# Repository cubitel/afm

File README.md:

DIY Atomic Force Microscope
---------------------------

DIY Atomic Force Microscope / Scanning Tunneling Microscope project.
More information can be found in [Project page](http://npk.cubitel.org/?/hardware/afm) (in Russian).

Please note that this project is under development yet.

### Hardware

Hardware folder contains hardware design files.

_Design tools_
- Schematic, PCB -- KiCAD
- 3D parts -- FreeCAD

### Firmware

Firmware folder contains firmware source files for STM32F407 controller.
Firmware using FreeRTOS and STM32 USB stack (bundled with the source tree).

### Software

Software folder contains control application source files.
Software using wxWidgets and libusb and designed to be cross-platform,
but current Makefile assumes Windows/MinGW.

_Build requirements_
- TDM-GCC
- wxWidgets
- libusb

### License
GPLv3

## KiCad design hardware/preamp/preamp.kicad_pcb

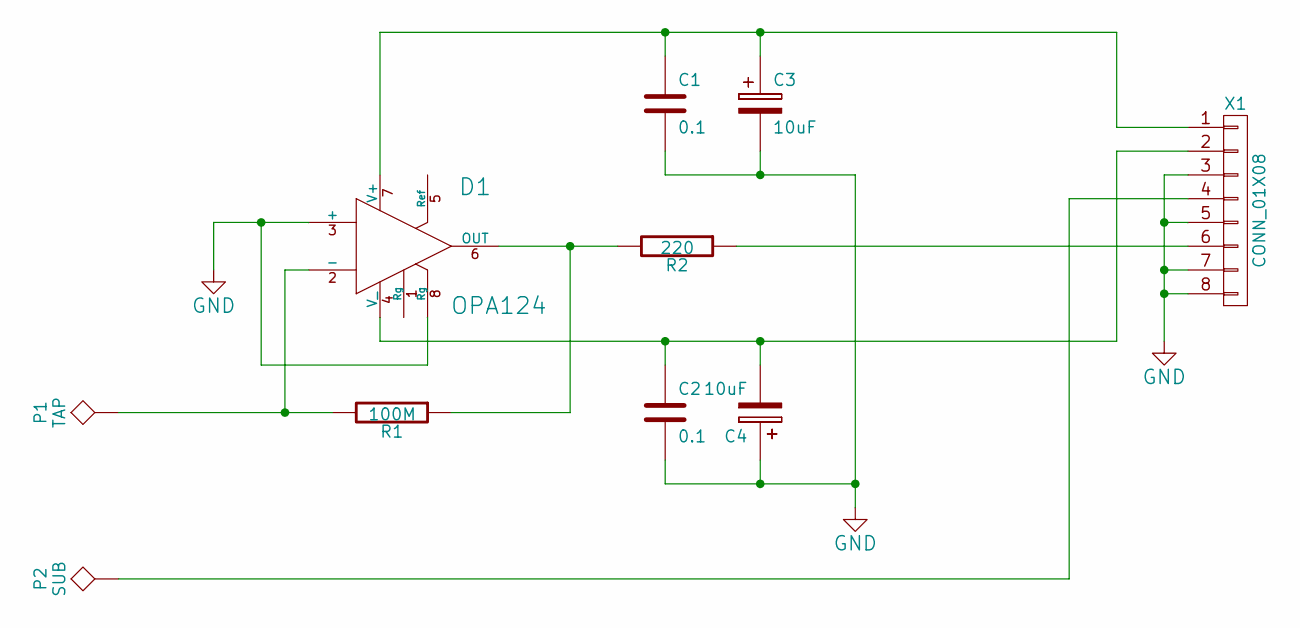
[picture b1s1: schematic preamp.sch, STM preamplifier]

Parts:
C1, C2: 0.1; C_0805
C3, C4: 10uF; TantalC_SizeA_EIA-3216_HandSoldering
D1: OPA124; SOIC-8-N
P1: TAP; Pin_Header_Straight_1x01
P2: SUB; Pin_Header_Straight_1x01
R1: 100M; R_0805
R2: 220; R_0805
X1: CONN_01X08; Pin_Header_Straight_1x08

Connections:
GND: C1.2, C2.2, C3.2, C4.1, D1.3 (+), D1.8 (Rg), X1.3, X1.5, X1.7, X1.8
unnamed: C1.1, C3.1, D1.7 (V+), X1.1
unnamed: C2.1, C4.2, D1.4 (V_), X1.2
unnamed: D1.2 (-), P1.1, R1.2
unnamed: D1.6 (OUT), R1.1, R2.2
unnamed: P2.1, X1.4
unnamed: R2.1, X1.6

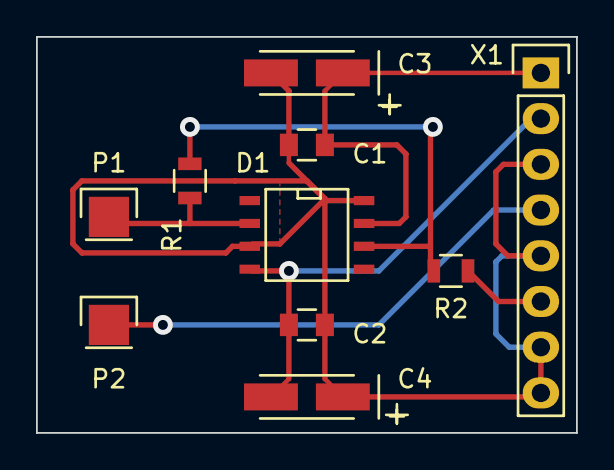
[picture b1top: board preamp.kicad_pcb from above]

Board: 2 copper layers, 30.0 x 22.0 mm, 10 parts (0 on the bottom side), 7 nets.

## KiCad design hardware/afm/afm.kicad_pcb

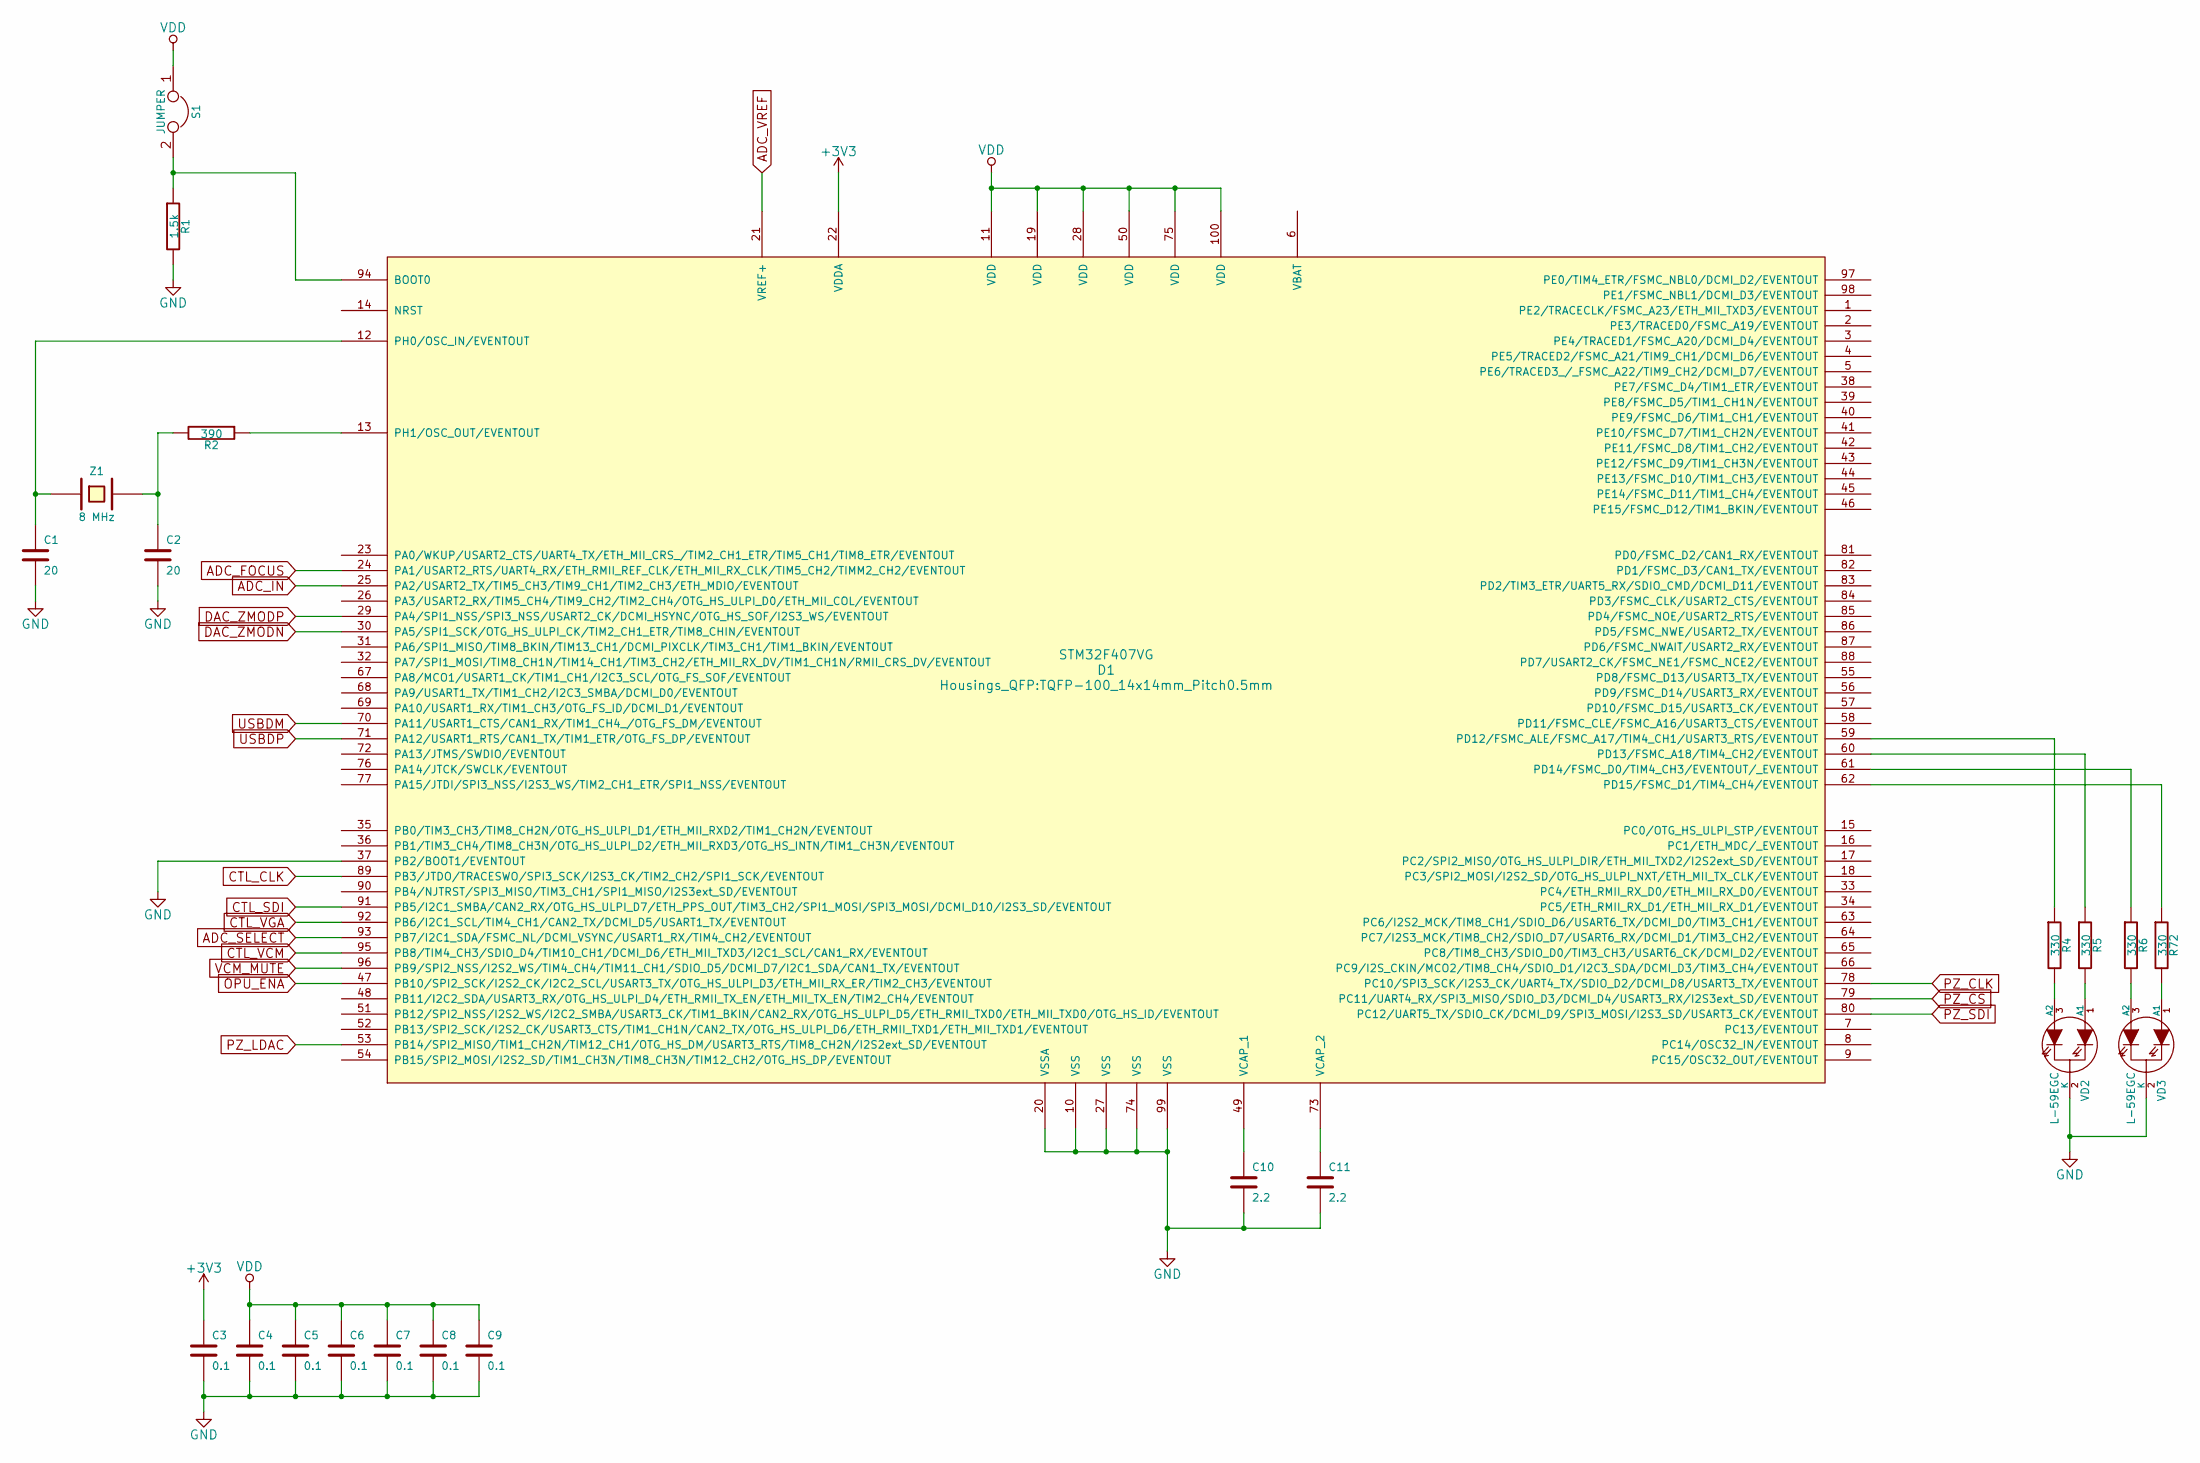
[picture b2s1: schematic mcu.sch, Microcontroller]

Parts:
C1, C2: 20; C_0603_HandSoldering
C3, C4, C5, C6, C7, C8, C9: 0.1; C_0603_HandSoldering
C10, C11: 2.2; C_0805_HandSoldering
D1: STM32F407VG; TQFP-100_14x14mm_Pitch0.5mm
R1: 1.5k; R_0603_HandSoldering
R2: 390; R_0603_HandSoldering
R4, R5, R6, R72: 330; R_0603_HandSoldering
S1: JUMPER; Pin_Header_Straight_1x02
VD2, VD3: L-59EGC; LED-5MM-3
Z1: 8 MHz; Crystal_HC49-SD_SMD

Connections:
+3V3: C3.1, D1.22 (VDDA); also elsewhere on the board
ADC_FOCUS: D1.24 (PA1/USART2_RTS/UART4_RX/ETH_RMII_REF_CL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); also elsewhere on the board
ADC_IN: D1.25 (PA2/USART2_TX/TIM5_CH3/TIM9_CH1/TIM2_CH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); also elsewhere on the board
ADC_SELECT: D1.93 (PB7/I2C1_SDA/FSMC_NL/DCMI_VSYNC/USART1_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); also elsewhere on the board
ADC_VREF: D1.21 (VREF+); also elsewhere on the board
CTL_CLK: D1.89 (PB3/JTDO/TRACESWO/SPI3_SCK/I2S3_CK/TIM2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); also elsewhere on the board
CTL_SDI: D1.91 (PB5/I2C1_SMBA/CAN2_RX/OTG_HS_ULPI_D7/ET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); also elsewhere on the board
CTL_VCM: D1.95 (PB8/TIM4_CH3/SDIO_D4/TIM10_CH1/DCMI_D6/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); also elsewhere on the board
CTL_VGA: D1.92 (PB6/I2C1_SCL/TIM4_CH1/CAN2_TX/DCMI_D5/U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); also elsewhere on the board
DAC_ZMODN: D1.30 (PA5/SPI1_SCK/OTG_HS_ULPI_CK/TIM2_CH1_ET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); also elsewhere on the board
DAC_ZMODP: D1.29 (PA4/SPI1_NSS/SPI3_NSS/USART2_CK/DCMI_HS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); also elsewhere on the board
GND: C1.2, C2.2, C3.2, C4.2, C5.2, C6.2, C7.2, C8.2, C9.2, C10.2, C11.2, D1.10 (VSS), D1.20 (VSSA), D1.27 (VSS), D1.37 (PB2/BOOT1/EVENTOUT), D1.74 (VSS), D1.99 (VSS), R1.2, VD2.2 (K), VD3.2 (K); also elsewhere on the board
unnamed: C1.1, D1.12 (PH0/OSC_IN/EVENTOUT), Z1.1
unnamed: C2.1, R2.2, Z1.2
unnamed: C10.1, D1.49 (VCAP_1)
unnamed: C11.1, D1.73 (VCAP_2)
unnamed: D1.13 (PH1/OSC_OUT/EVENTOUT), R2.1
unnamed: D1.59 (PD12/FSMC_ALE/FSMC_A17/TIM4_CH1/USART3_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), R4.1
unnamed: D1.60 (PD13/FSMC_A18/TIM4_CH2/EVENTOUT), R5.1
unnamed: D1.61 (PD14/FSMC_D0/TIM4_CH3/EVENTOUT/_EVENTOUT), R6.1
unnamed: D1.62 (PD15/FSMC_D1/TIM4_CH4/EVENTOUT), R72.1
unnamed: D1.94 (BOOT0), R1.1, S1.2
unnamed: R4.2, VD2.3 (A2)
unnamed: R5.2, VD2.1 (A1)
unnamed: R6.2, VD3.3 (A2)
unnamed: R72.2, VD3.1 (A1)
OPU_ENA: D1.47 (PB10/SPI2_SCK/I2S2_CK/I2C2_SCL/USART3_T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); also elsewhere on the board
PZ_CLK: D1.78 (PC10/SPI3_SCK/I2S3_CK/UART4_TX/SDIO_D2/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); also elsewhere on the board
PZ_CS: D1.79 (PC11/UART4_RX/SPI3_MISO/SDIO_D3/DCMI_D4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); also elsewhere on the board
PZ_LDAC: D1.53 (PB14/SPI2_MISO/TIM1_CH2N/TIM12_CH1/OTG_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); also elsewhere on the board
PZ_SDI: D1.80 (PC12/UART5_TX/SDIO_CK/DCMI_D9/SPI3_MOSI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); also elsewhere on the board
USBDM: D1.70 (PA11/USART1_CTS/CAN1_RX/TIM1_CH4_/OTG_F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); also elsewhere on the board
USBDP: D1.71 (PA12/USART1_RTS/CAN1_TX/TIM1_ETR/OTG_FS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); also elsewhere on the board
VCM_MUTE: D1.96 (PB9/SPI2_NSS/I2S2_WS/TIM4_CH4/TIM11_CH1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); also elsewhere on the board
VDD: C4.1, C5.1, C6.1, C7.1, C8.1, C9.1, D1.11 (VDD), D1.19 (VDD), D1.28 (VDD), D1.50 (VDD), D1.75 (VDD), D1.100 (VDD), S1.1; also elsewhere on the board

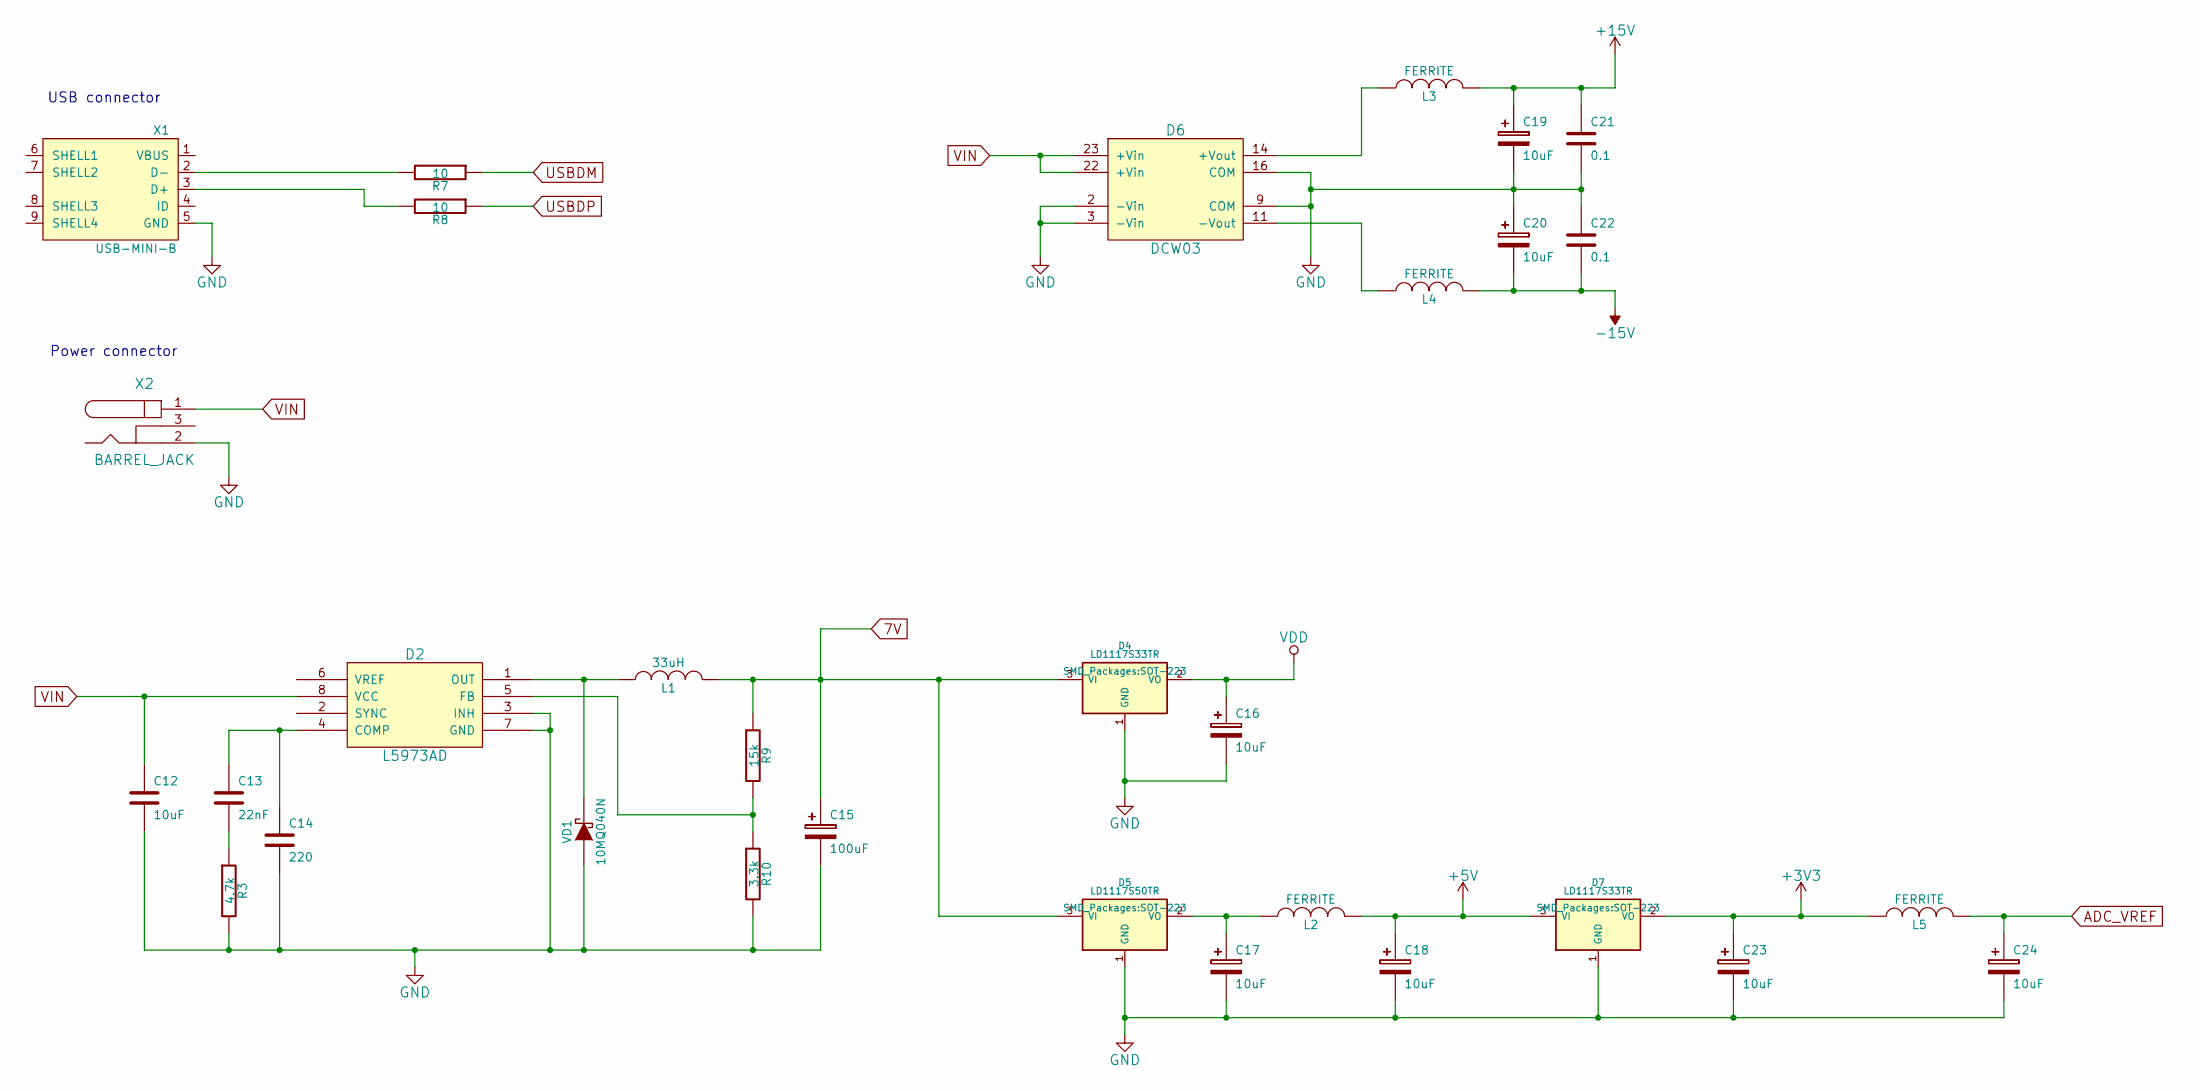
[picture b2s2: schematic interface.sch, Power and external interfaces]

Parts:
C12: 10uF; C_1206_HandSoldering
C13: 22nF; C_0603_HandSoldering
C14: 220; C_0603_HandSoldering
C15: 100uF; TantalC_SizeD_EIA-7343_HandSoldering
C16, C17, C18, C23, C24: 10uF; TantalC_SizeB_EIA-3528_HandSoldering
C19, C20: 10uF; TantalC_SizeD_EIA-7343_HandSoldering
C21, C22: 0.1; C_0603_HandSoldering
D2: L5973AD; SOIC-8-1EP_3.9x4.9mm_Pitch1.27mm
D4, D7: LD1117S33TR; SOT-223
D5: LD1117S50TR; SOT-223
D6: DCW03; DIP-24__600
L1: 33uH; Neosid_Inductor_SM-PIC0612H
L2, L3, L4, L5: FERRITE; R_1206_HandSoldering
R3: 4.7k; R_0603_HandSoldering
R7, R8: 10; R_0603_HandSoldering
R9: 15k; R_0603_HandSoldering
R10: 3.3k; R_0603_HandSoldering
VD1: 10MQ040N; Diode-SMA_Handsoldering
X1: USB-MINI-B; USB_Mini-B
X2: BARREL_JACK; JACK_ALIM

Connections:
7V: C15.1, D4.3 (VI), D5.3 (VI), L1.2, R9.1
+3V3: C23.1, D7.2 (VO), L5.1; also elsewhere on the board
+5V: C18.1, D7.3 (VI), L2.2; also elsewhere on the board
+15V: C19.1, C21.1, L3.2; also elsewhere on the board
-15V: C20.2, C22.2, L4.2; also elsewhere on the board
ADC_VREF: C24.1, L5.2; also elsewhere on the board
GND: C12.2, C14.2, C15.2, C16.2, C17.2, C18.2, C19.2, C20.1, C21.2, C22.1, C23.2, C24.2, D2.3 (INH), D2.7 (GND), D4.1 (GND), D5.1 (GND), D6.2 (-Vin), D6.3 (-Vin), D6.9 (COM), D6.16 (COM), D7.1 (GND), R3.2, R10.2, VD1.1 (A), X1.5 (GND), X2.2; also elsewhere on the board
unnamed: C13.1, C14.1, D2.4 (COMP)
unnamed: C13.2, R3.1
unnamed: C17.1, D5.2 (VO), L2.1
unnamed: D2.1 (OUT), L1.1, VD1.2 (K)
unnamed: D2.5 (FB), R9.2, R10.1
unnamed: D6.11 (-Vout), L4.1
unnamed: D6.14 (+Vout), L3.1
unnamed: R7.2, X1.2 (D-)
unnamed: R8.2, X1.3 (D+)
USBDM: R7.1; also elsewhere on the board
USBDP: R8.1; also elsewhere on the board
VDD: C16.1, D4.2 (VO); also elsewhere on the board
VIN: C12.1, D2.8 (VCC), D6.22 (+Vin), D6.23 (+Vin), X2.1

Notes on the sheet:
USB connector
Power connector

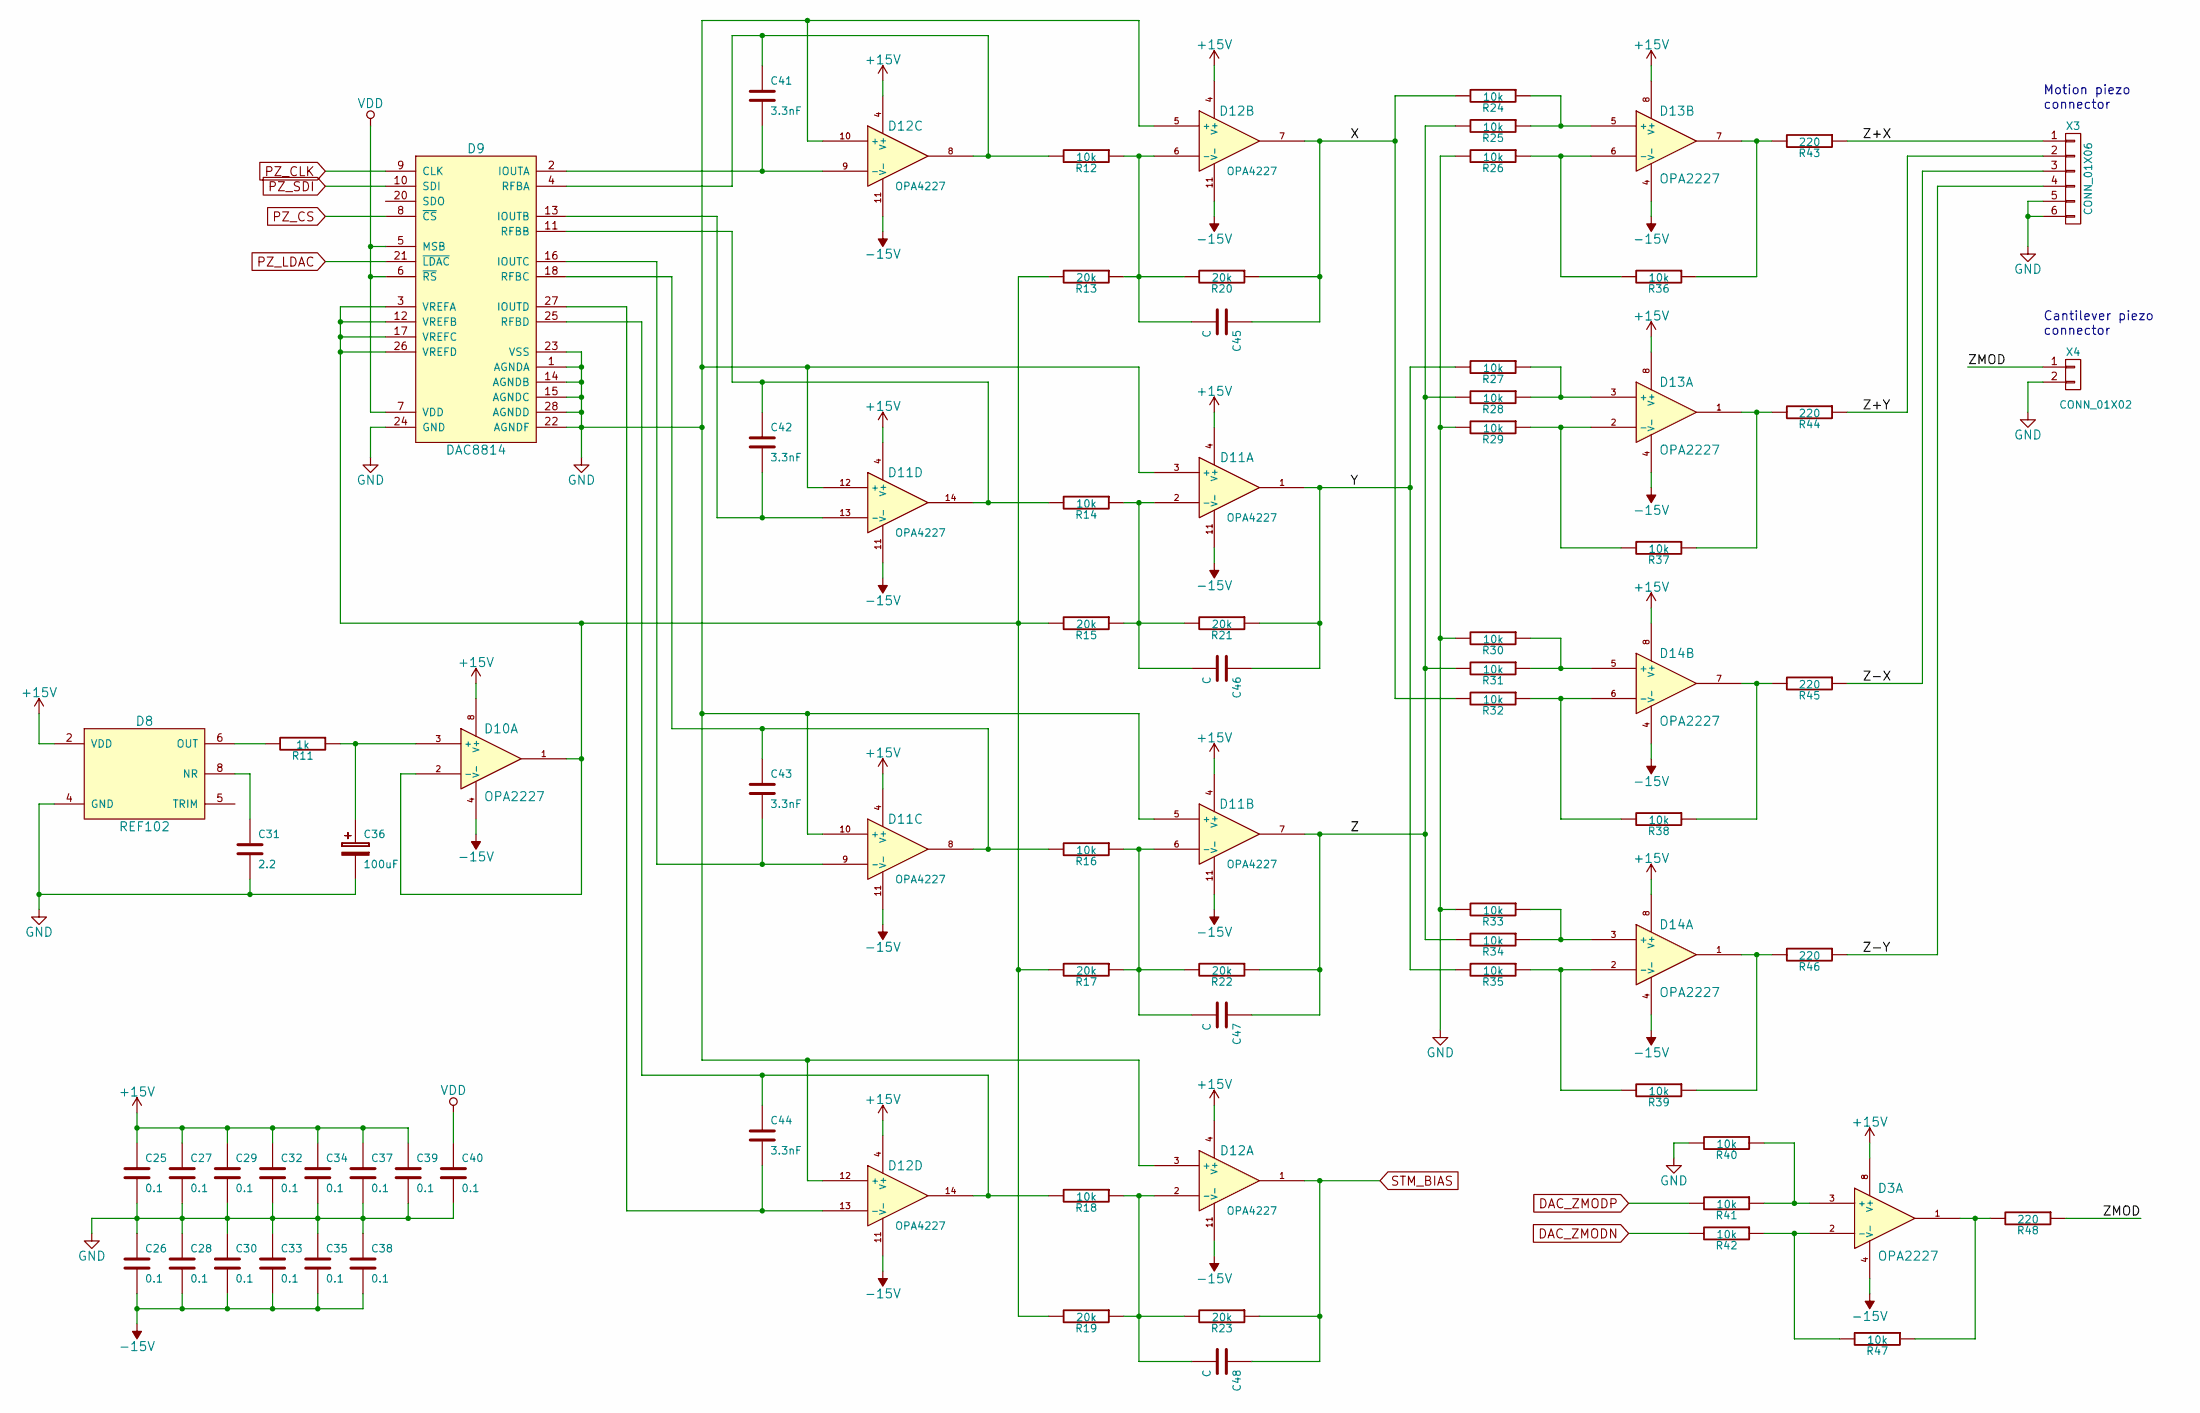
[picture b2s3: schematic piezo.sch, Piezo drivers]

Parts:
C25, C26, C27, C28, C29, C30, C32, C33, C34, C35, C37, C38, C39, C40: 0.1; C_0603_HandSoldering
C31: 2.2; C_0603_HandSoldering
C36: 100uF; TantalC_SizeD_EIA-7343_HandSoldering
C41, C42, C43, C44: 3.3nF; C_0603_HandSoldering
C45, C46, C47, C48: C; C_0603_HandSoldering
D3, D10, D13, D14: OPA2227; SOIC-8-N
D8: REF102; SOIC-8-N
D9: DAC8814; SSOP-28_5.3x10.2mm_Pitch0.65mm
D11, D12: OPA4227; SOIC-14_N
R11: 1k; R_0603_HandSoldering
R12, R14, R16, R18, R24, R25, R26, R27, R28, R29, R30, R31, R32, R33, R34, R35, R36, R37, R38, R39, R40, R41, R42, R47: 10k; R_0603_HandSoldering
R13, R15, R17, R19, R20, R21, R22, R23: 20k; R_0603_HandSoldering
R43, R44, R45, R46, R48: 220; R_0603_HandSoldering
X3: CONN_01X06; Pin_Header_Straight_1x06
X4: CONN_01X02; Pin_Header_Straight_1x02

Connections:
+15V: C25.1, C27.1, C29.1, C32.1, C34.1, C37.1, C39.1, D3.8 (V+), D8.2 (VDD), D10.8 (V+), D11.4 (V+), D12.4 (V+), D13.8 (V+), D14.8 (V+); also elsewhere on the board
-15V: C26.2, C28.2, C30.2, C33.2, C35.2, C38.2, D3.4 (V-), D10.4 (V-), D11.11 (V-), D12.11 (V-), D13.4 (V-), D14.4 (V-); also elsewhere on the board
/Piezo drivers/X: C45.1, D12.7, R20.1, R24.2, R32.2
/Piezo drivers/Y: C46.1, D11.1, R21.1, R27.2, R35.2
/Piezo drivers/Z: C47.1, D11.7, R22.1, R25.2, R28.2, R31.2, R34.2
/Piezo drivers/Z+X: R43.1, X3.1
/Piezo drivers/Z+Y: R44.1, X3.2
/Piezo drivers/Z-X: R45.1, X3.3
/Piezo drivers/Z-Y: R46.1, X3.4
/Piezo drivers/ZMOD: R48.1, X4.1
DAC_ZMODN: R42.2; also elsewhere on the board
DAC_ZMODP: R41.2; also elsewhere on the board
GND: C25.2, C26.1, C27.2, C28.1, C29.2, C30.1, C31.2, C32.2, C33.1, C34.2, C35.1, C36.2, C37.2, C38.1, C39.2, C40.2, D8.4 (GND), D9.1 (AGNDA), D9.14 (AGNDB), D9.15 (AGNDC), D9.22 (AGNDF), D9.23 (VSS), D9.24 (GND), D9.28 (AGNDD), D11.3 (+), D11.5 (+), D11.10 (+), D11.12 (+), D12.3 (+), D12.5 (+), D12.10 (+), D12.12 (+), R26.2, R29.2, R30.2, R33.2, R40.2, X3.5, X3.6, X4.2; also elsewhere on the board
unnamed: C31.1, D8.8 (NR)
unnamed: C36.1, D10.3 (+), R11.1
unnamed: C41.1, D9.4 (RFBA), D12.8, R12.2
unnamed: C41.2, D9.2 (IOUTA), D12.9 (-)
unnamed: C42.1, D9.11 (RFBB), D11.14, R14.2
unnamed: C42.2, D9.13 (IOUTB), D11.13 (-)
unnamed: C43.1, D9.18 (RFBC), D11.8, R16.2
unnamed: C43.2, D9.16 (IOUTC), D11.9 (-)
unnamed: C44.1, D9.25 (RFBD), D12.14, R18.2
unnamed: C44.2, D9.27 (IOUTD), D12.13 (-)
unnamed: C45.2, D12.6 (-), R12.1, R13.1, R20.2
unnamed: C46.2, D11.2 (-), R14.1, R15.1, R21.2
unnamed: C47.2, D11.6 (-), R16.1, R17.1, R22.2
unnamed: C48.2, D12.2 (-), R18.1, R19.1, R23.2
unnamed: D3.1, R47.1, R48.2
unnamed: D3.2 (-), R42.1, R47.2
unnamed: D3.3 (+), R40.1, R41.1
unnamed: D8.6 (OUT), R11.2
unnamed: D9.3 (VREFA), D9.12 (VREFB), D9.17 (VREFC), D9.26 (VREFD), D10.1, D10.2 (-), R13.2, R15.2, R17.2, R19.2
unnamed: D13.1, R37.1, R44.2
unnamed: D13.2 (-), R29.1, R37.2
unnamed: D13.3 (+), R27.1, R28.1
unnamed: D13.5 (+), R24.1, R25.1
unnamed: D13.6 (-), R26.1, R36.2
unnamed: D13.7, R36.1, R43.2
unnamed: D14.1, R39.1, R46.2
unnamed: D14.2 (-), R35.1, R39.2
unnamed: D14.3 (+), R33.1, R34.1
unnamed: D14.5 (+), R30.1, R31.1
unnamed: D14.6 (-), R32.1, R38.2
unnamed: D14.7, R38.1, R45.2
PZ_CLK: D9.9 (CLK); also elsewhere on the board
PZ_CS: D9.8 (~CS); also elsewhere on the board
PZ_LDAC: D9.21 (~LDAC); also elsewhere on the board
PZ_SDI: D9.10 (SDI); also elsewhere on the board
STM_BIAS: C48.1, D12.1, R23.1; also elsewhere on the board
VDD: C40.1, D9.5 (MSB), D9.6 (~RS), D9.7 (VDD); also elsewhere on the board

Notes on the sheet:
Motion piezo connector
Cantilever piezo connector

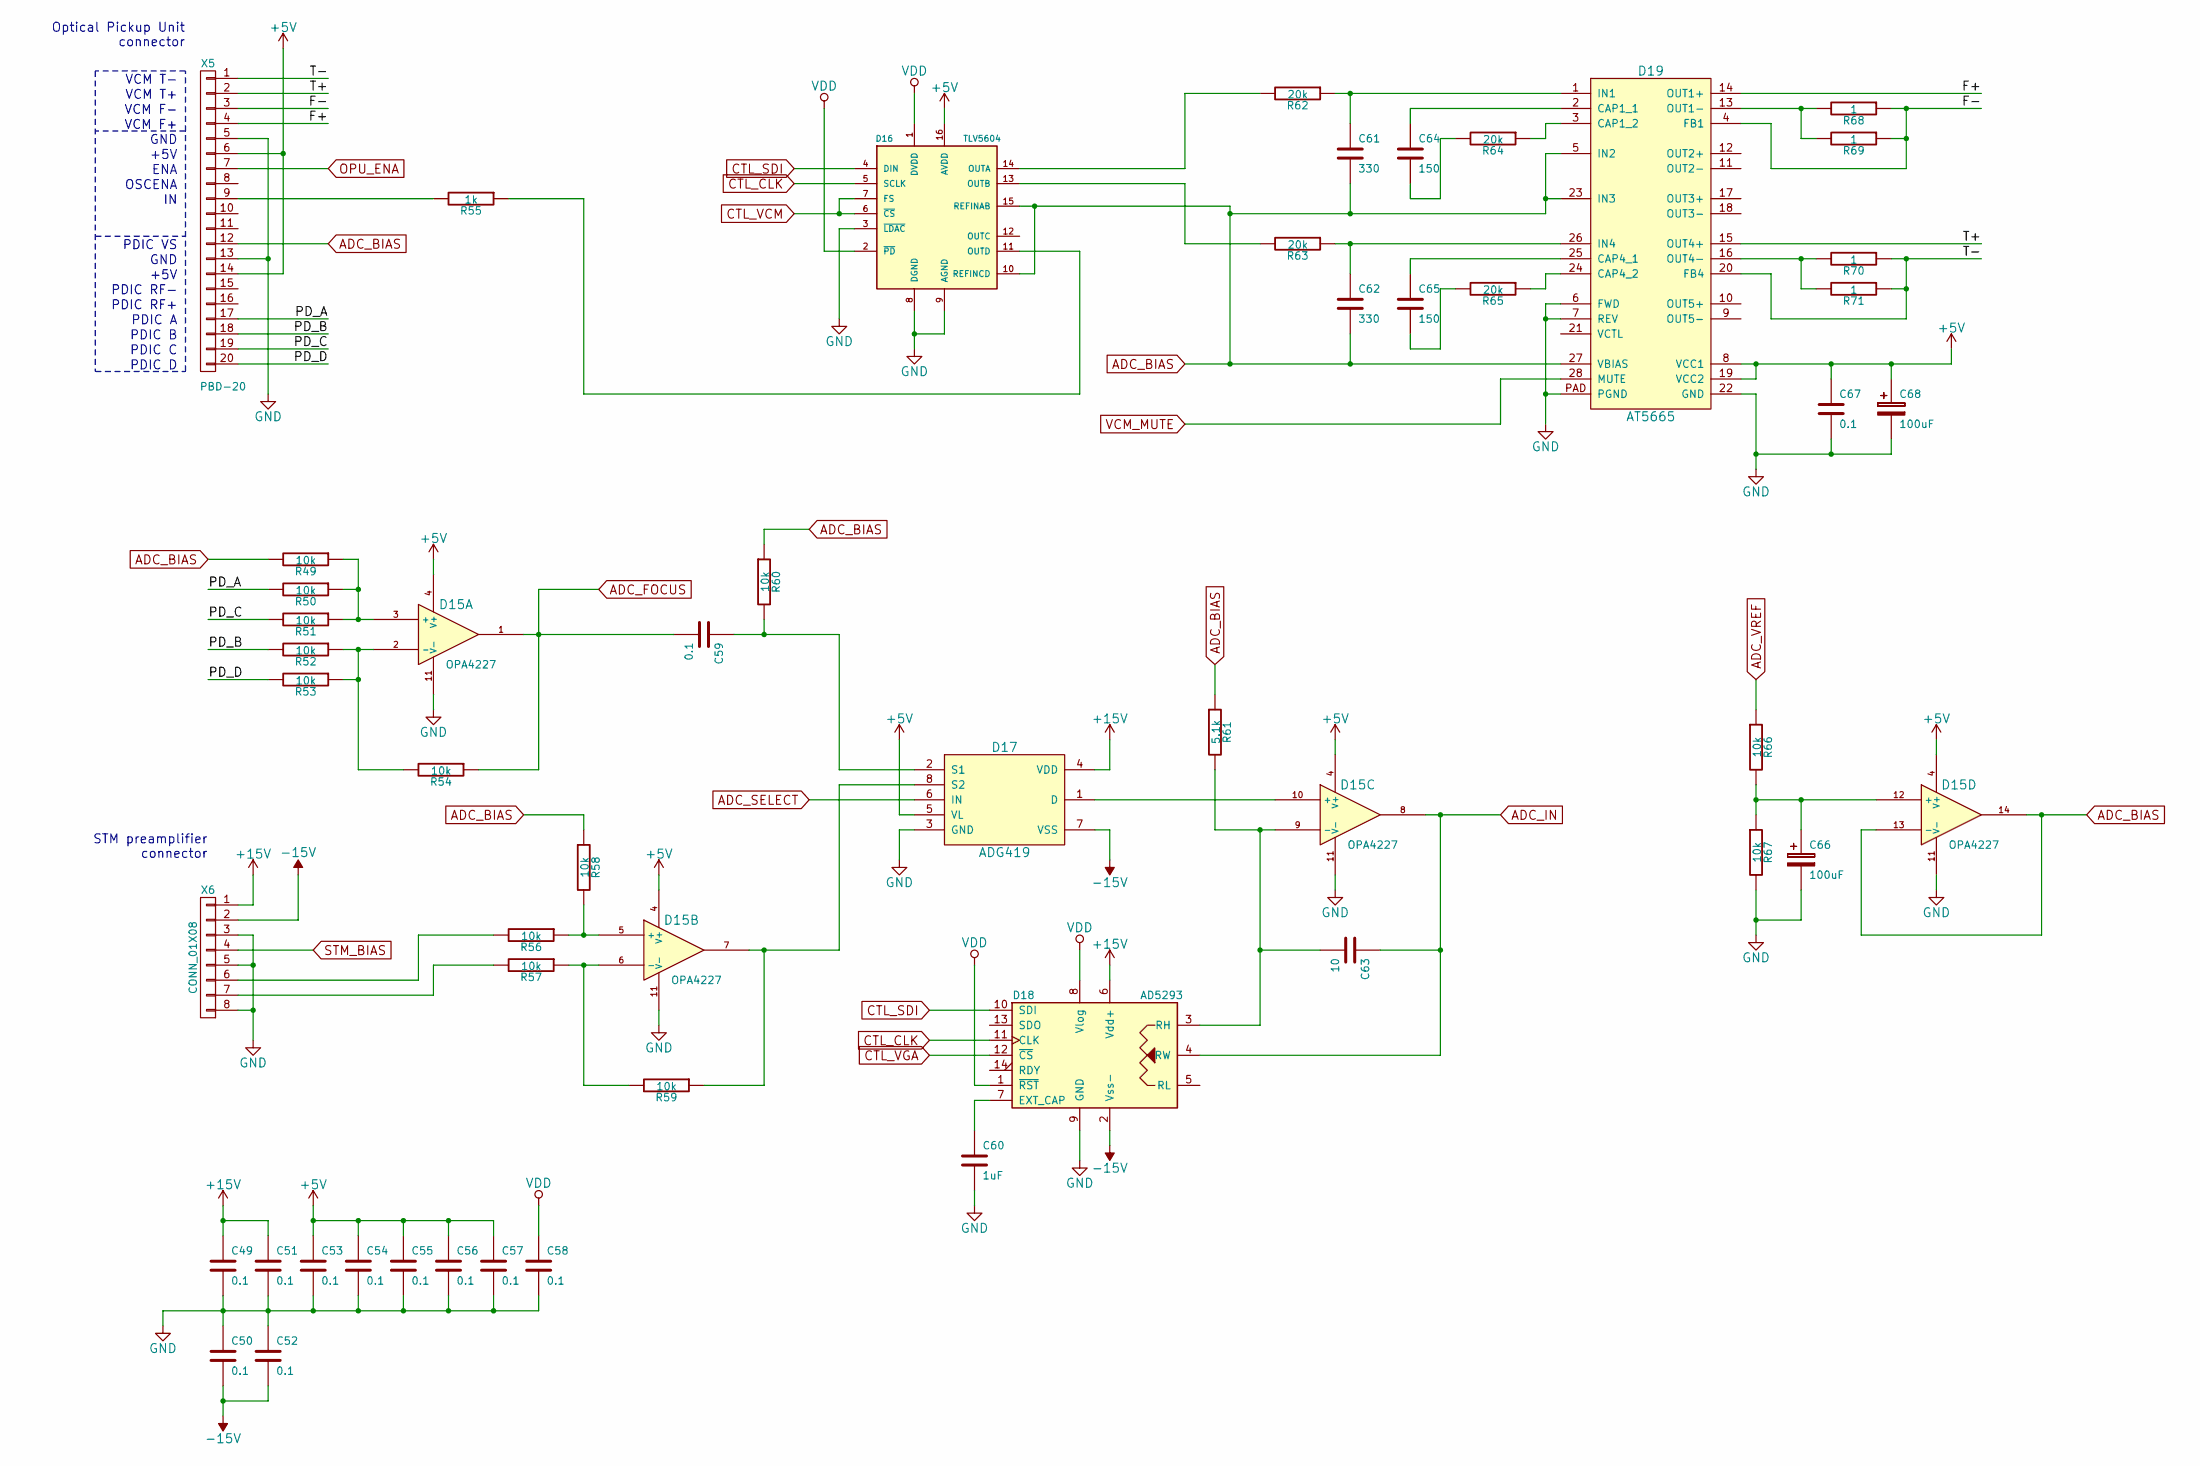
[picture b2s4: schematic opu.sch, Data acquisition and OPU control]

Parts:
C49, C50, C51, C52, C53, C54, C55, C56, C57, C58, C59, C67: 0.1; C_0603_HandSoldering
C60: 1uF; C_0805_HandSoldering
C61, C62: 330; C_0603_HandSoldering
C63: 10; C_0603_HandSoldering
C64, C65: 150; C_0603_HandSoldering
C66, C68: 100uF; TantalC_SizeD_EIA-7343_HandSoldering
D15: OPA4227; SOIC-14_N
D16: TLV5604; SOIC-16_3.9x9.9mm_Pitch1.27mm
D17: ADG419; SOIC-8_3.9x4.9mm_Pitch1.27mm
D18: AD5293; TSSOP-14_4.4x5mm_Pitch0.65mm
D19: AT5665; SOIC-28
R49, R50, R51, R52, R53, R54, R56, R57, R58, R59, R60, R66, R67: 10k; R_0603_HandSoldering
R55: 1k; R_0603_HandSoldering
R61: 5.1k; R_0603_HandSoldering
R62, R63, R64, R65: 20k; R_0603_HandSoldering
R68, R69, R70, R71: 1; R_0805_HandSoldering
X5: PBD-20; Pin_Header_Straight_2x10
X6: CONN_01X08; Pin_Header_Straight_1x08

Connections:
+5V: C53.1, C54.1, C55.1, C56.1, C57.1, C67.1, C68.1, D15.4 (V+), D16.16 (AVDD), D17.5 (VL), D19.8 (VCC1), D19.19 (VCC2), X5.6, X5.14; also elsewhere on the board
+15V: C49.1, C51.1, D17.4 (VDD), D18.6 (Vdd+), X6.1; also elsewhere on the board
-15V: C50.2, C52.2, D17.7 (VSS), D18.2 (Vss-), X6.2; also elsewhere on the board
/OPU interface/F+: D19.14 (OUT1+), X5.4
/OPU interface/F-: D19.4 (FB1), R68.1, R69.1, X5.3
/OPU interface/PD_A: R50.2, X5.17
/OPU interface/PD_B: R52.2, X5.18
/OPU interface/PD_C: R51.2, X5.19
/OPU interface/PD_D: R53.2, X5.20
/OPU interface/T+: D19.15 (OUT4+), X5.2
/OPU interface/T-: D19.20 (FB4), R70.1, R71.1, X5.1
ADC_BIAS: C61.2, C62.2, D15.13 (-), D15.14, D16.10 (REFINCD), D16.15 (REFINAB), D19.5 (IN2), D19.23 (IN3), D19.27 (VBIAS), R49.2, R58.1, R60.1, R61.1, X5.12
ADC_FOCUS: C59.2, D15.1, R54.1; also elsewhere on the board
ADC_IN: C63.1, D15.8, D18.4 (RW); also elsewhere on the board
ADC_SELECT: D17.6 (IN); also elsewhere on the board
ADC_VREF: R66.1; also elsewhere on the board
CTL_CLK: D16.5 (SCLK), D18.11 (CLK); also elsewhere on the board
CTL_SDI: D16.4 (DIN), D18.10 (SDI); also elsewhere on the board
CTL_VCM: D16.6 (~CS), D16.7 (FS); also elsewhere on the board
CTL_VGA: D18.12 (~CS~); also elsewhere on the board
GND: C49.2, C50.1, C51.2, C52.1, C53.2, C54.2, C55.2, C56.2, C57.2, C58.2, C60.2, C66.2, C67.2, C68.2, D15.11 (V-), D16.3 (~LDAC), D16.8 (DGND), D16.9 (AGND), D17.3 (GND), D18.9 (GND), D19.6 (FWD), D19.7 (REV), D19.22 (GND), D19.PAD (PGND), R67.2, X5.5, X5.13, X6.3, X6.5, X6.8; also elsewhere on the board
unnamed: C59.1, D17.2 (S1), R60.2
unnamed: C60.1, D18.7 (EXT_CAP)
unnamed: C61.1, D19.1 (IN1), R62.1
unnamed: C62.1, D19.26 (IN4), R63.1
unnamed: C63.2, D15.9 (-), D18.3 (RH), R61.2
unnamed: C64.1, D19.2 (CAP1_1)
unnamed: C64.2, R64.2
unnamed: C65.1, D19.25 (CAP4_1)
unnamed: C65.2, R65.2
unnamed: C66.1, D15.12 (+), R66.2, R67.1
unnamed: D15.2 (-), R52.1, R53.1, R54.2
unnamed: D15.3 (+), R49.1, R50.1, R51.1
unnamed: D15.5 (+), R56.1, R58.2
unnamed: D15.6 (-), R57.1, R59.2
unnamed: D15.7, D17.8 (S2), R59.1
unnamed: D15.10 (+), D17.1 (D)
unnamed: D16.11 (OUTD), R55.1
unnamed: D16.13 (OUTB), R63.2
unnamed: D16.14 (OUTA), R62.2
unnamed: D19.3 (CAP1_2), R64.1
unnamed: D19.13 (OUT1-), R68.2, R69.2
unnamed: D19.16 (OUT4-), R70.2, R71.2
unnamed: D19.24 (CAP4_2), R65.1
unnamed: R55.2, X5.9
unnamed: R56.2, X6.6
unnamed: R57.2, X6.7
OPU_ENA: X5.7; also elsewhere on the board
STM_BIAS: X6.4; also elsewhere on the board
VCM_MUTE: D19.28 (MUTE); also elsewhere on the board
VDD: C58.1, D16.1 (DVDD), D16.2 (~PD), D18.1 (~RST~), D18.8 (Vlog); also elsewhere on the board

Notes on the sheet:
VCM T-
VCM T+
VCM F-
VCM F+
GND
+5V
PDIC D
PDIC C
PDIC B
PDIC A
PDIC VS
ENA
OSCENA
PDIC RF+
PDIC RF-
Optical Pickup Unit connector
STM preamplifier connector

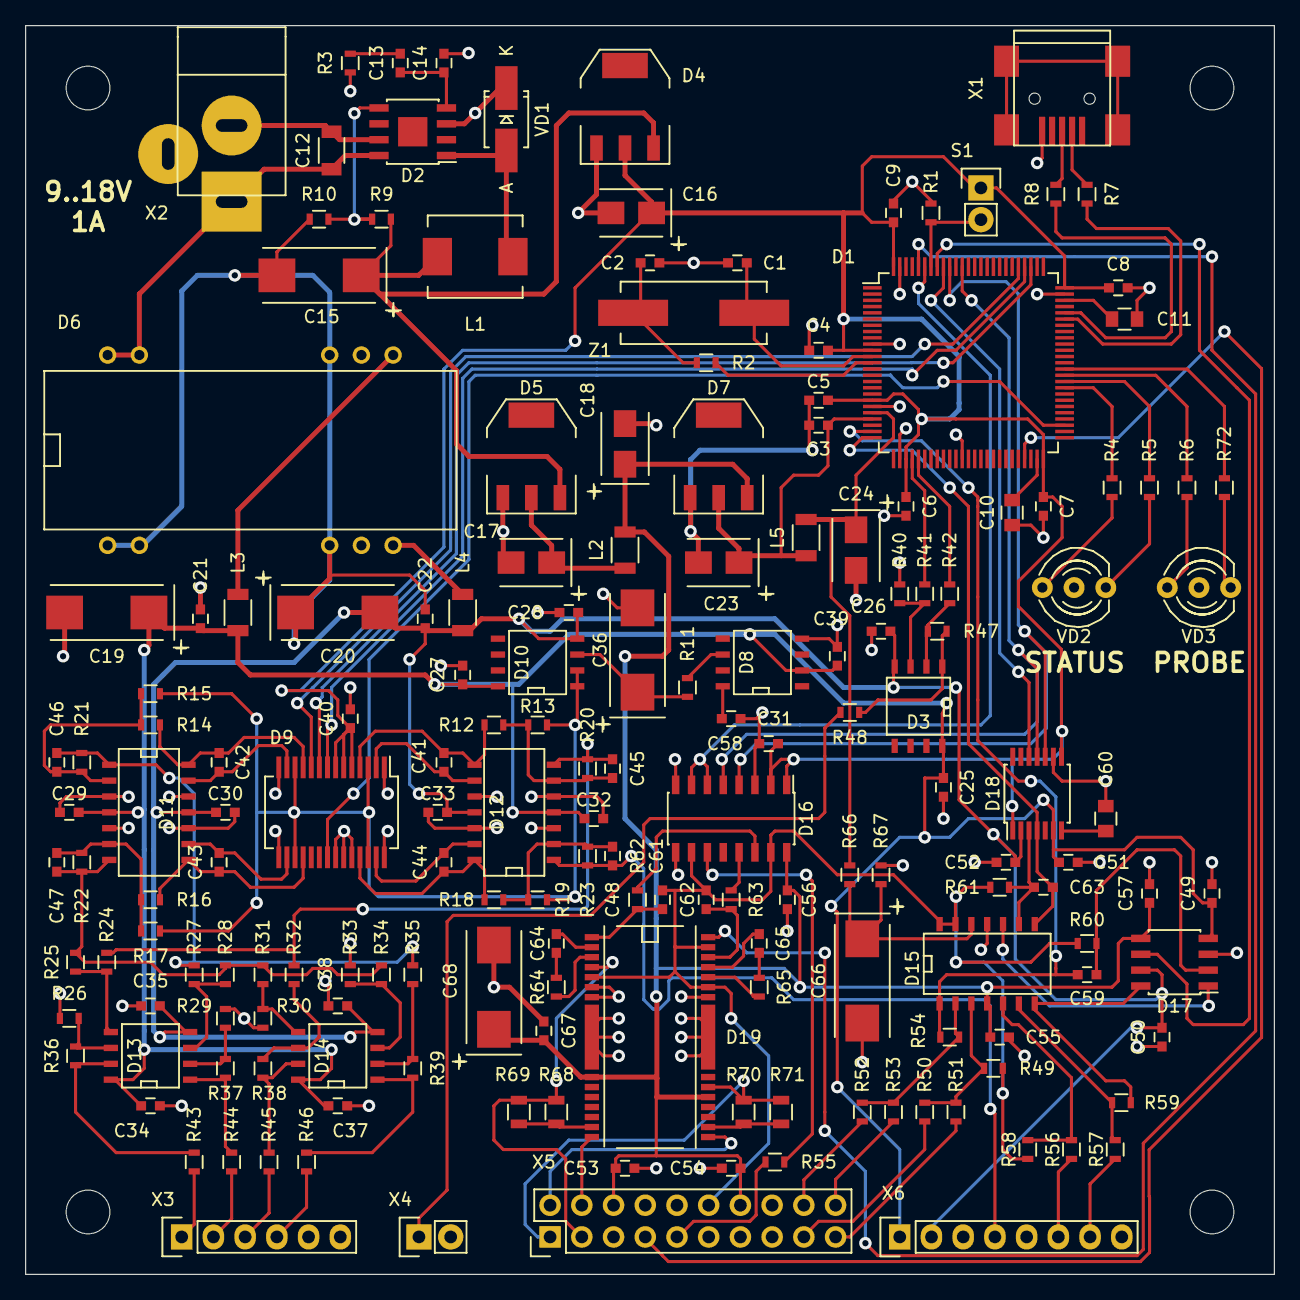
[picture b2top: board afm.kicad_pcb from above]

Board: 2 copper layers, 100.0 x 100.0 mm, 175 parts (0 on the bottom side), 124 nets.

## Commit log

2015-07-19 README update
2015-07-22 Update gitignore
2015-07-22 Piezo DAC moved from SPI2 to SPI3
2015-07-22 Initial piezo control
2015-07-24 PCB trace completed
2015-08-08 Changed origin point
